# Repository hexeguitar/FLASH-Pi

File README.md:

FLASH-Pi
========
##### SPI & I2C level converter and bus driver for RaspberryPi Zero
The main goal of this project was to create a versatile programmer for various EEPROM and FLASH memory chips using flashrom and wiringPi packages.

![alt text][pic1]

#### Background & origins
In order fo fix an HDMI controller board I had to reprogram the onboard 25-series SPI FLASH memory containing a corrupted firmware image. None of my standalone programmers could erase the chip, so i tried to use the RasPi Zero + Flashrom as a programmer. Flashrom 0.9.9 did detect the chip, but still couldn't erase it. As it turned out, this memory had a non volatile protection bit set, clearing it was not implemented in the software. Using the wiringPi i was able to clear the bit, reprogram the chip and finally set the protection bit back. This gave me an idea that a RasPi Zero W + Flashrom + WiringPi, Python + an addon board with level converters/buffers could serve as a quite powerful, versatile and yet very compact SPI FLASH programmer. Ontop of that i decided to add a similar level converter for the I2C bus using the PCA9617A chip.  
The main function of the FLASH-Pi is to **convert the voltage levels** and **isolate** the SPI and I2C buses on the RaspberryPi Zero.

![alt text][pic2]

#### Features:
* SPI0 bus: level translation between the RPi's native 3.3V and one of the listed below:
    - 5V
    - 3.3V
    - 1.8V
    - externally supplied voltage in range from 1.6V to 5.5V
* I2C1 bus: level translation between the RPi's native 3.3V and one of the listed below:
    - 5V
    - 3.3V
    - 1.8V
    - externally supplied voltage in range from 0.8V to 5.5V
* Overcurrent protection (polyfuses) on the 5V and 3.3V rails supplied by the RPi
* Labelled RaspberryPi GPIO pins for easy wiring and experiments.

![alt text][pic3]

#### Circuit design:
Initially i used the TXS0104 chip to level shift SPI bus, which turned out to be a trap (always read the datasheet carefully!). The condition of VCCA (3.3V Raspi side) > VCCB (Target) could not be met for 1.8V output level. Since the SPI lines does not have to be bidirectional i ended up using four SN74LV1T125 buffers specifically designed to up/down translate the levels in wide ranges.  
RaspberryPi provides 5V and 3.3V power rails. Both rails are protected with polyfuses, 100mA for the 5V line and 50mA for the 3.3V one. The 1.8V rail is generated with the MCP1700T-1802 voltage regulator. Target voltage level is set with a 4 way slider switch.  
The 4th option uses an externally supplied target voltage and is intended to use with in-circuit operation.  
I2C section is actually a stock application of the PCA9617A chip. 1k5 pull-ups are provided on both sides.

![alt text][pic5]

#### Software
After doing the usual startup houskeeping (changing the password, setting locales, enabling SPI, I2C, serial port, VNC, Wifi config, etc...) on a fresh Raspbian image i usually remove a few packages that will not be much of use in this application. This will free up some space on the SD card.
```
sudo apt-get remove --purge wolfram-engine scratch minecraft-pi sonic-pi claws-mail bluej python-pygame greenfoot
sudo apt-get clean
sudo apt-get autoremove
```
The next step is to install the wiringPi library. The instruction on how to do that is provided on the authors site:
http://wiringpi.com/download-and-install/

Installing [flashrom](https://www.flashrom.org)   is as easy as:
```
sudo apt-get install flashrom
```
It is probalby worth to install and setup a shared folder with ***samba*** for easy file exchange over the network.

#### Usage
In most cases the RasPi will be run headless and accessed via:
* SSH for command line operation
* VNC viewer using a remote desktop  

![alt text][pic6]

I opted to use the RasPi Zero W for it's compact size and built in WiFi, accessing it remotely from my main PC or laptop. Of course, a regular model Zero will work, too. Especially using an Ethernet over USB-OTG option seems to be quite useful idea - making the device an USB programmer.  

#### PCBs
PCBs are available from OSH Park:  

<a href="https://www.oshpark.com/shared_projects/ycM4MtRF"></img></a>  

![alt text][pic4]

------
(c) 11.2017 by Piotr Zapart  
www.hexeguitar.com

License:
Creative Commons - Attribution - ShareAlike 3.0  
[http://creativecommons.org/licenses/by-sa/3.0/](http://creativecommons.org/licenses/by-sa/3.0/)

[pic1]: pics/FlashPi_V2_0.jpg "FLASH-Pi"

[pic2]: pics/FlashPi_V2_2.jpg "FLASH-Pi"
[pic3]: pics/FlashPi_V2_3.jpg "FLASH-Pi"
[pic4]: pics/FlashPi_V2_PCB.jpg "FLASH-Pi PCB"
[pic5]: design_files/FlashPi_V2_schm.png "FLASH-Pi schematic"
[pic6]: pics/FlashPi_VNC3sm.png "Using Flash-Pi via VNC"

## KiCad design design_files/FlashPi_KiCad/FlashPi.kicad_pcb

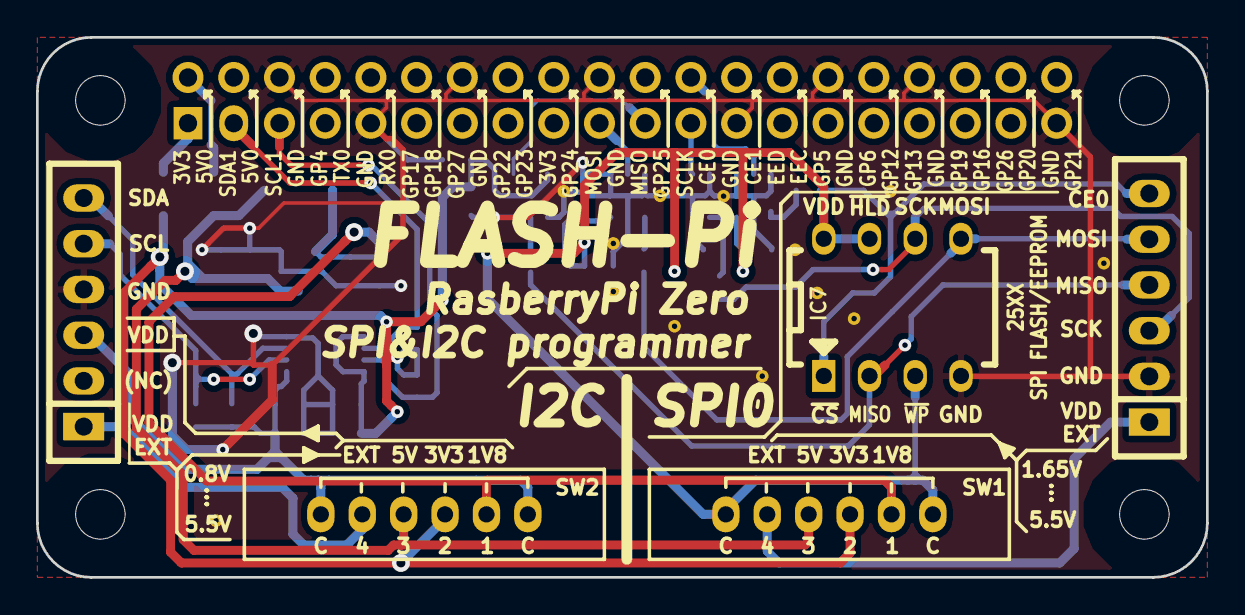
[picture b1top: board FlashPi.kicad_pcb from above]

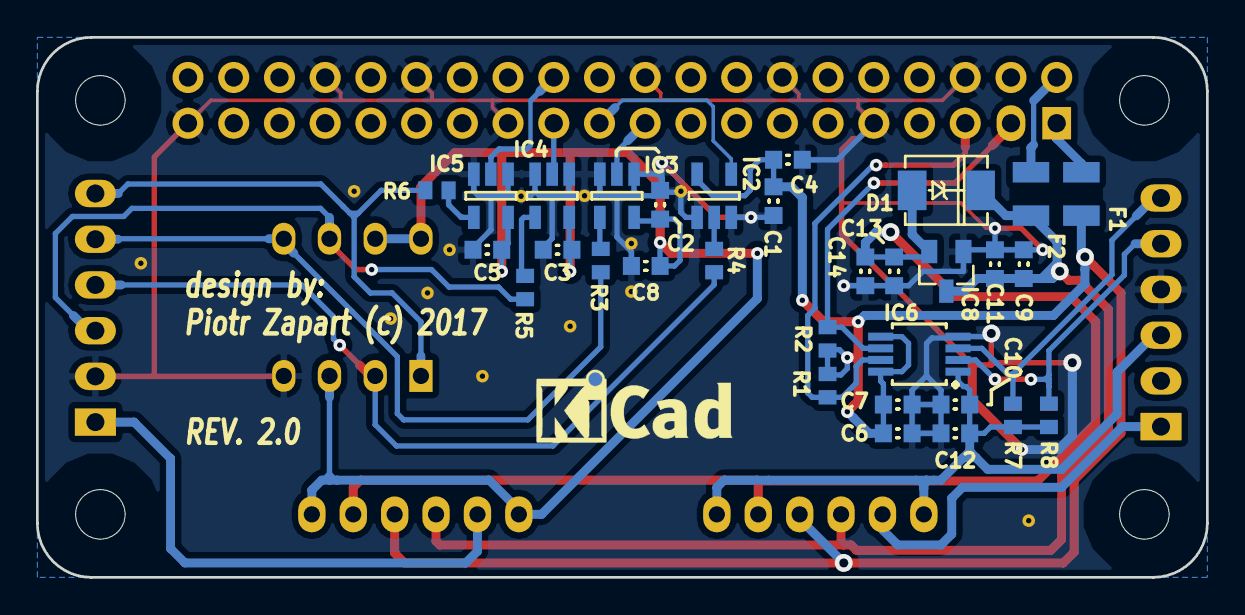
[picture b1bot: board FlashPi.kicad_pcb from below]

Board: 2 copper layers, 65.0 x 30.0 mm, 50 parts (31 on the bottom side), 26 nets.

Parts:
C1, C6, C8, C9, C12, C14: 1u; CAPC_0603_1608X86N
C2, C3, C4, C5, C7, C10, C11, C13: 100n; CAPC_0603_1608X86N
D1: SS14; DO-214-AC_SMA
F1: 50mA; Fuse_SMD1206_Reflow
F2: 100mA; Fuse_SMD1206_Reflow
IC1: RPi_A+_B+_2B_Hat; z_RPiZero_Hat_NPTH
IC2, IC3, IC4, IC5: SN74LV1T125_SOT23_5; SOT23-5
IC6: PCA9617A; SOP65P490X110-8AN
IC7: 25LC_EEPROM; DIP-8
IC8: MCP1700T-1802E/TT; SOT-23
P1, P2: CONN_01X06; CONN-100MIL-F-1x6
R1, R2, R7, R8: 1k5; RESC_0603_1508X63N
R3, R4, R5, R6: 33R; RESC_0603_1508X63N
SW1, SW2: 1P4T_generic_switch; SLB1470_1P4T_slideSW
Via0703_GND, Via0703_GND#2, Via0703_GND#3, Via0703_GND#4, Via0703_GND#5, Via0703_GND#6, Via0703_GND#7, Via0703_GND#8, Via0703_GND#9, Via0703_GND#10, Via0703_GND#11, Via0703_GND#12, Via0703_GND#13: VAL**; Via0703_GND

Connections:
/I2C_SCL: IC1.5, IC6.7, R1.2
/I2C_SDA: IC1.3, IC6.6, R2.2
/SCL_EXT: IC6.2, P2.5, R8.1
/SDA_EXT: IC6.3, P2.6, R7.1
/SPI0_CE0: IC1.24, IC5.2
/SPI0_CE0_EXT: IC7.1, P1.6, R6.1
/SPI0_MISO: IC1.21, IC2.4
/SPI0_MISO_EXT: IC7.2, P1.4, R4.1
/SPI0_MOSI: IC1.19, IC3.2
/SPI0_MOSI_EXT: IC7.5, P1.5, R3.1
/SPI0_SCK: IC1.23, IC4.2
/SPI0_SCK_EXT: IC7.6, P1.3, R5.1
/V18: C13.1, C14.1, D1.1, IC8.2, SW1.2, SW2.2
/V33: C1.1, C4.1, C6.1, C7.1, F1.1, IC2.5, IC6.5, IC6.8, R1.1, R2.1, SW1.3, SW2.3
/V50: C9.1, C11.1, D1.2, F2.2, IC8.3, SW1.4, SW2.4
/VCC_I2C: C10.1, C12.1, IC6.1, P2.3, R7.2, R8.2, SW2.1
/VCC_SPI: C2.1, C3.1, C5.1, C8.1, IC3.5, IC4.5, IC5.5, IC7.3, IC7.7, IC7.8, SW1.1
/VEXT_I2C: P2.1, SW2.5
/VEXT_SPI: P1.1, SW1.5
GND: C1.2, C2.2, C3.2, C4.2, C5.2, C6.2, C7.2, C8.2, C9.2, C10.2, C11.2, C12.2, C13.2, C14.2, IC1.6, IC1.9, IC1.14, IC1.20, IC1.25, IC1.30, IC1.34, IC1.39, IC2.1, IC2.3, IC3.1, IC3.3, IC4.1, IC4.3, IC5.1, IC5.3, IC6.4, IC7.4, IC8.1, P1.2, P2.4, Via0703_GND.1, Via0703_GND#2.1, Via0703_GND#3.1, Via0703_GND#4.1, Via0703_GND#5.1, Via0703_GND#6.1, Via0703_GND#7.1, Via0703_GND#8.1, Via0703_GND#9.1, Via0703_GND#10.1, Via0703_GND#11.1, Via0703_GND#12.1, Via0703_GND#13.1
unnamed: F1.2, IC1.1
unnamed: F2.1, IC1.2
unnamed: IC2.2, R4.2
unnamed: IC3.4, R3.2
unnamed: IC4.4, R5.2
unnamed: IC5.4, R6.2

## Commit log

2017-11-09 :boom::camel: Added .gitattributes & .gitignore files
2017-11-12 readme update

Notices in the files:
design_files/FlashPi_KiCad/FlashPi.kicad_pcb:
design by:
Piotr Zapart (c) 2017
